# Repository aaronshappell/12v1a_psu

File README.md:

# 12v1a_psu
A simple linear regulated 12V 1A power supply.

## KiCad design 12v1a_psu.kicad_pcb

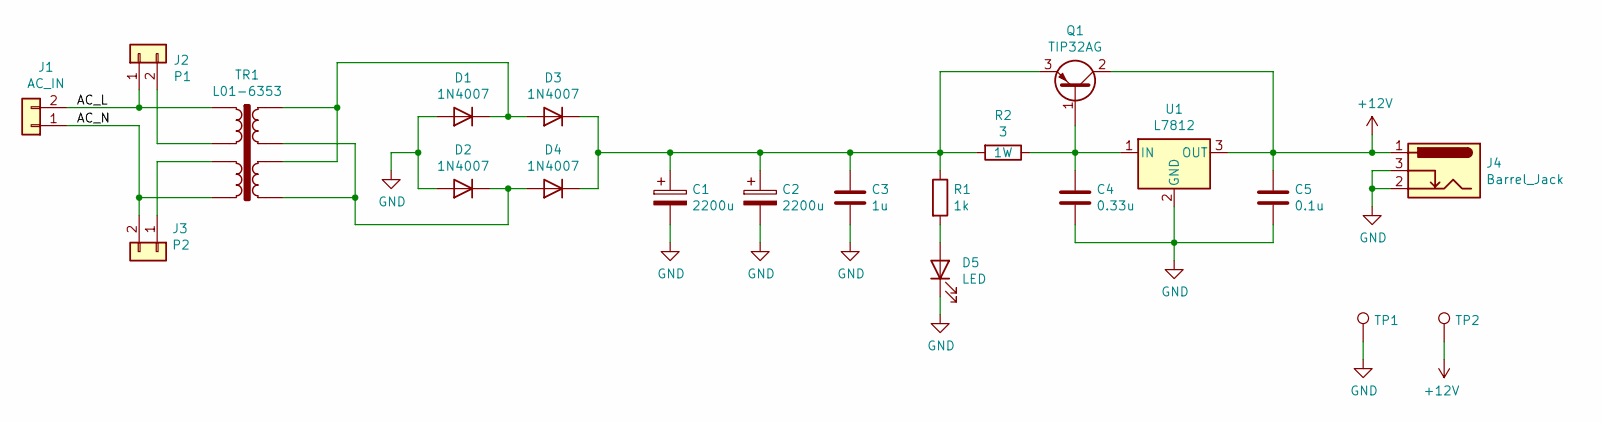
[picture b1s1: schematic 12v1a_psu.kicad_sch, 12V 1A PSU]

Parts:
C1, C2: 2200u; CP_Radial_D16.0mm_P7.50mm
C3: 1u; C_Rect_L18.0mm_W8.0mm_P15.00mm_FKS3_FKP3
C4: 0.33u; C_Rect_L7.2mm_W3.5mm_P5.00mm_FKS2_FKP2_MKS2_MKP2
C5: 0.1u; C_Rect_L7.2mm_W2.5mm_P5.00mm_FKS2_FKP2_MKS2_MKP2
D1, D2, D3, D4: 1N4007; D_DO-41_SOD81_P10.16mm_Horizontal
D5: LED; LED_D5.0mm_Horizontal_O1.27mm_Z3.0mm
J1: AC_IN; SolderWire-0.75sqmm_1x02_P4.8mm_D1.25mm_OD2.3mm
J2: P1; SolderWire-0.75sqmm_1x02_P4.8mm_D1.25mm_OD2.3mm
J3: P2; SolderWire-0.75sqmm_1x02_P4.8mm_D1.25mm_OD2.3mm
J4: Barrel_Jack; BarrelJack_Horizontal
Q1: TIP32AG; TO-220-3_Vertical
R1: 1k; R_Axial_DIN0207_L6.3mm_D2.5mm_P10.16mm_Horizontal
R2: 3; R_Axial_DIN0207_L6.3mm_D2.5mm_P10.16mm_Horizontal
TP1: TestPoint; TestPoint_THTPad_2.0x2.0mm_Drill1.0mm
TP2: TestPoint; TestPoint_THTPad_D2.0mm_Drill1.0mm
TR1: L01-6353; L01-6363
U1: L7812; TO-220-3_Vertical

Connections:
+12V: C5.1, J4.1, Q1.2 (C), TP2.1, U1.3 (OUT)
/AC_L: J1.2, J2.1, TR1.1
/AC_N: J1.1, J3.2, TR1.4
GND: C1.2, C2.2, C3.2, C4.2, C5.2, D1.2 (A), D2.2 (A), D5.1 (K), J4.2, J4.3, TP1.1, U1.2 (GND)
unnamed: C1.1, C2.1, C3.1, D3.1 (K), D4.1 (K), Q1.3 (E), R1.1, R2.2
unnamed: C4.1, Q1.1 (B), R2.1, U1.1 (IN)
unnamed: D1.1 (K), D3.2 (A), TR1.6, TR1.8
unnamed: D2.1 (K), D4.2 (A), TR1.5, TR1.7
unnamed: D5.2 (A), R1.2
unnamed: J2.2, TR1.2
unnamed: J3.1, TR1.3

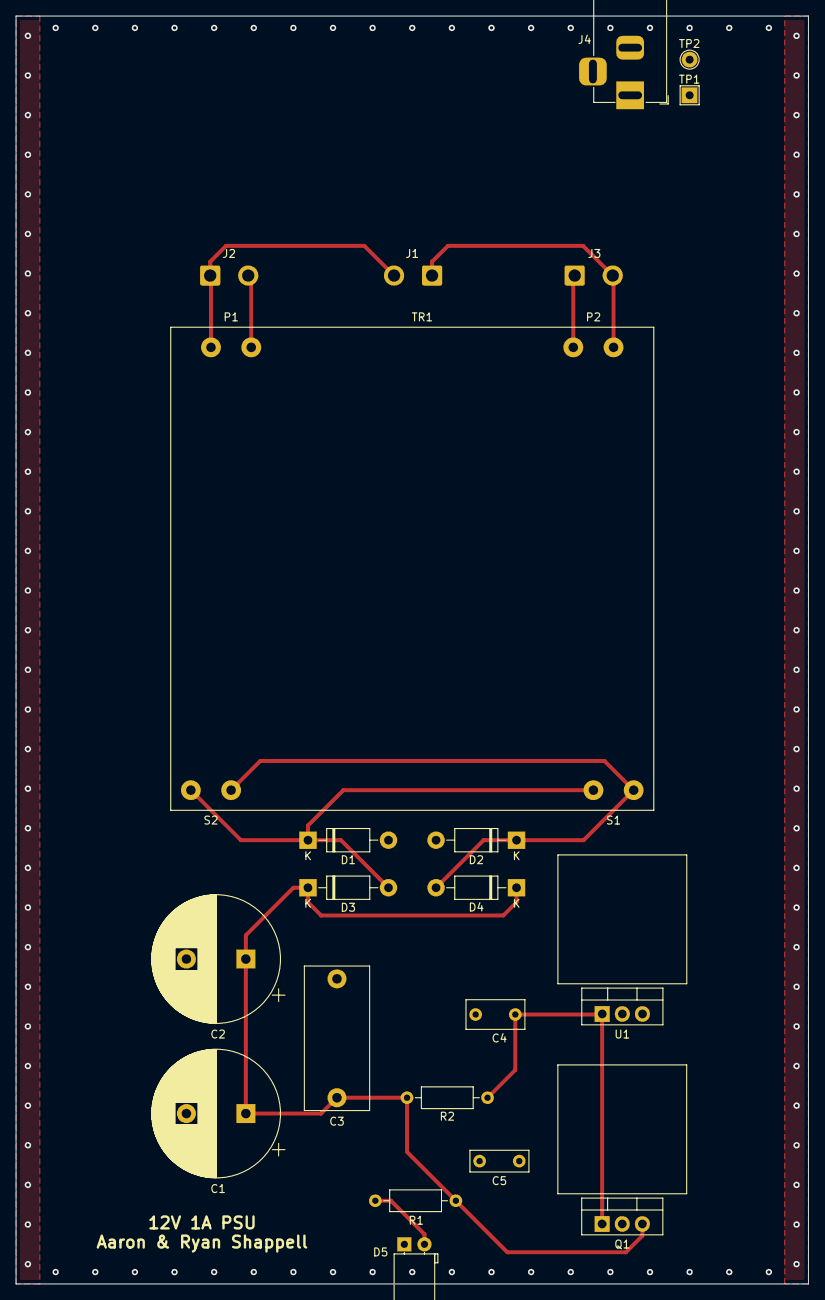
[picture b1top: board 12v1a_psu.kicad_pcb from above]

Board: 4 copper layers, 100.0 x 160.0 mm, 21 parts (0 on the bottom side), 11 nets.

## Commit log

2019-05-06 Finish schematic and start on pcb
2019-05-06 Work on pcb layout
2019-05-06 reorganize and finalize board size
2019-05-06 Add traces and ground plane
2019-05-07 Resize board for switch and ac input
2019-05-07 add graphic and small adjustments
2019-05-07 generate gerber files
2020-11-06 Remove plots folder
2020-11-06 Add blank LTspice simulation file
2020-11-06 Update gitignore
2020-11-07 Add simulation schematic
2020-11-16 Add filter caps, misc changes
2020-11-16 Clean up symbol/footprint libs, add cad models
2020-11-16 Remove fp-info-cache
2020-11-16 Fix cap value
2020-11-16 Chose bjt for reg, picked footprints
2020-11-17 Add parts list, add case and ac receptable step files
2020-11-23 Component and trace layout
2020-11-23 Move step file
2020-12-04 Add switch blockout for assembly check, misc layout change
2020-12-04 Add cat silkscreen, update sheet info
2021-01-06 Add gerbers
2022-10-04 Commit to kicad 6, fix libraries
2022-10-04 Add blank projects for pcb panels, add basic model for cutout
